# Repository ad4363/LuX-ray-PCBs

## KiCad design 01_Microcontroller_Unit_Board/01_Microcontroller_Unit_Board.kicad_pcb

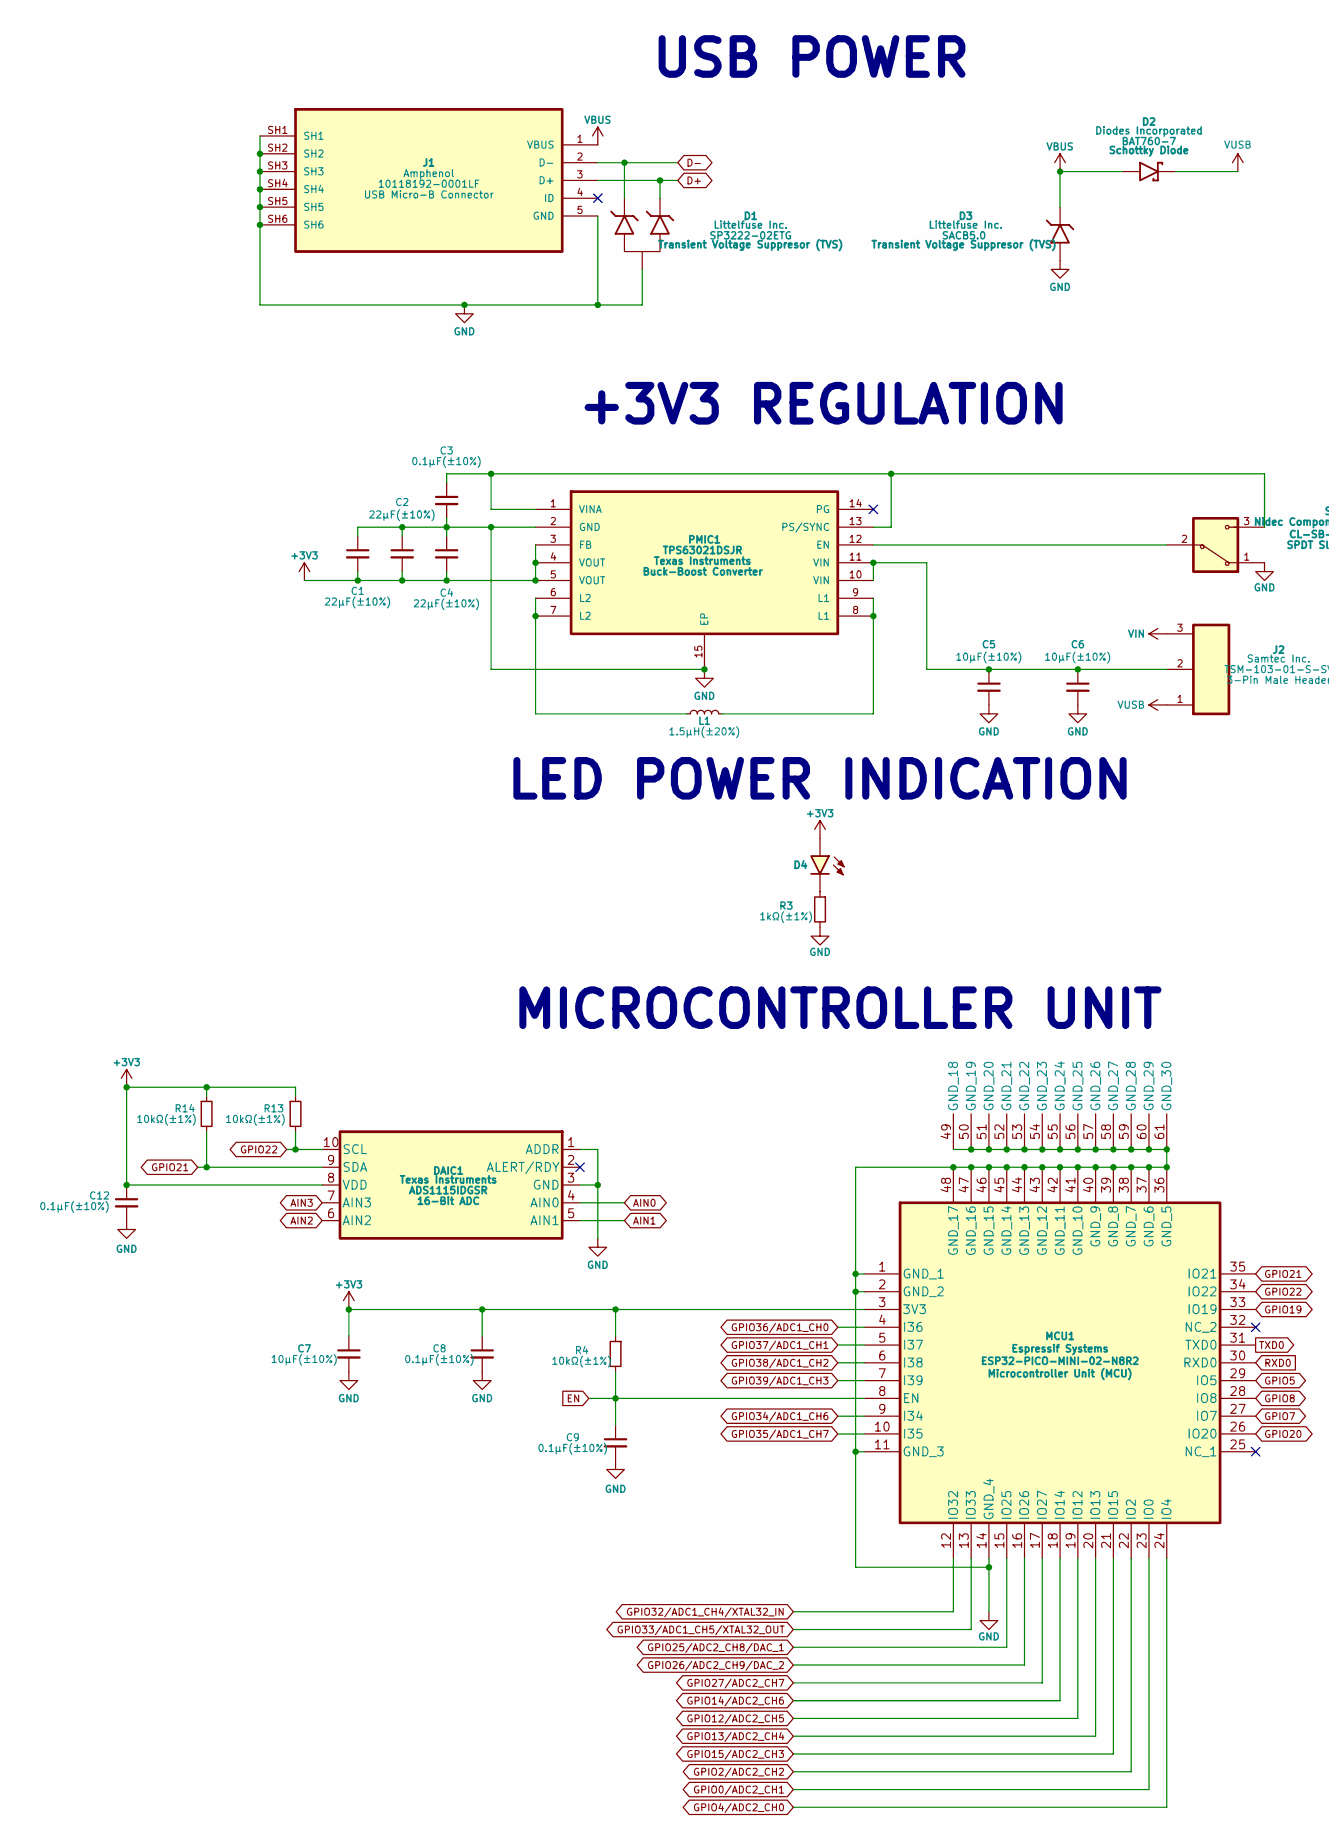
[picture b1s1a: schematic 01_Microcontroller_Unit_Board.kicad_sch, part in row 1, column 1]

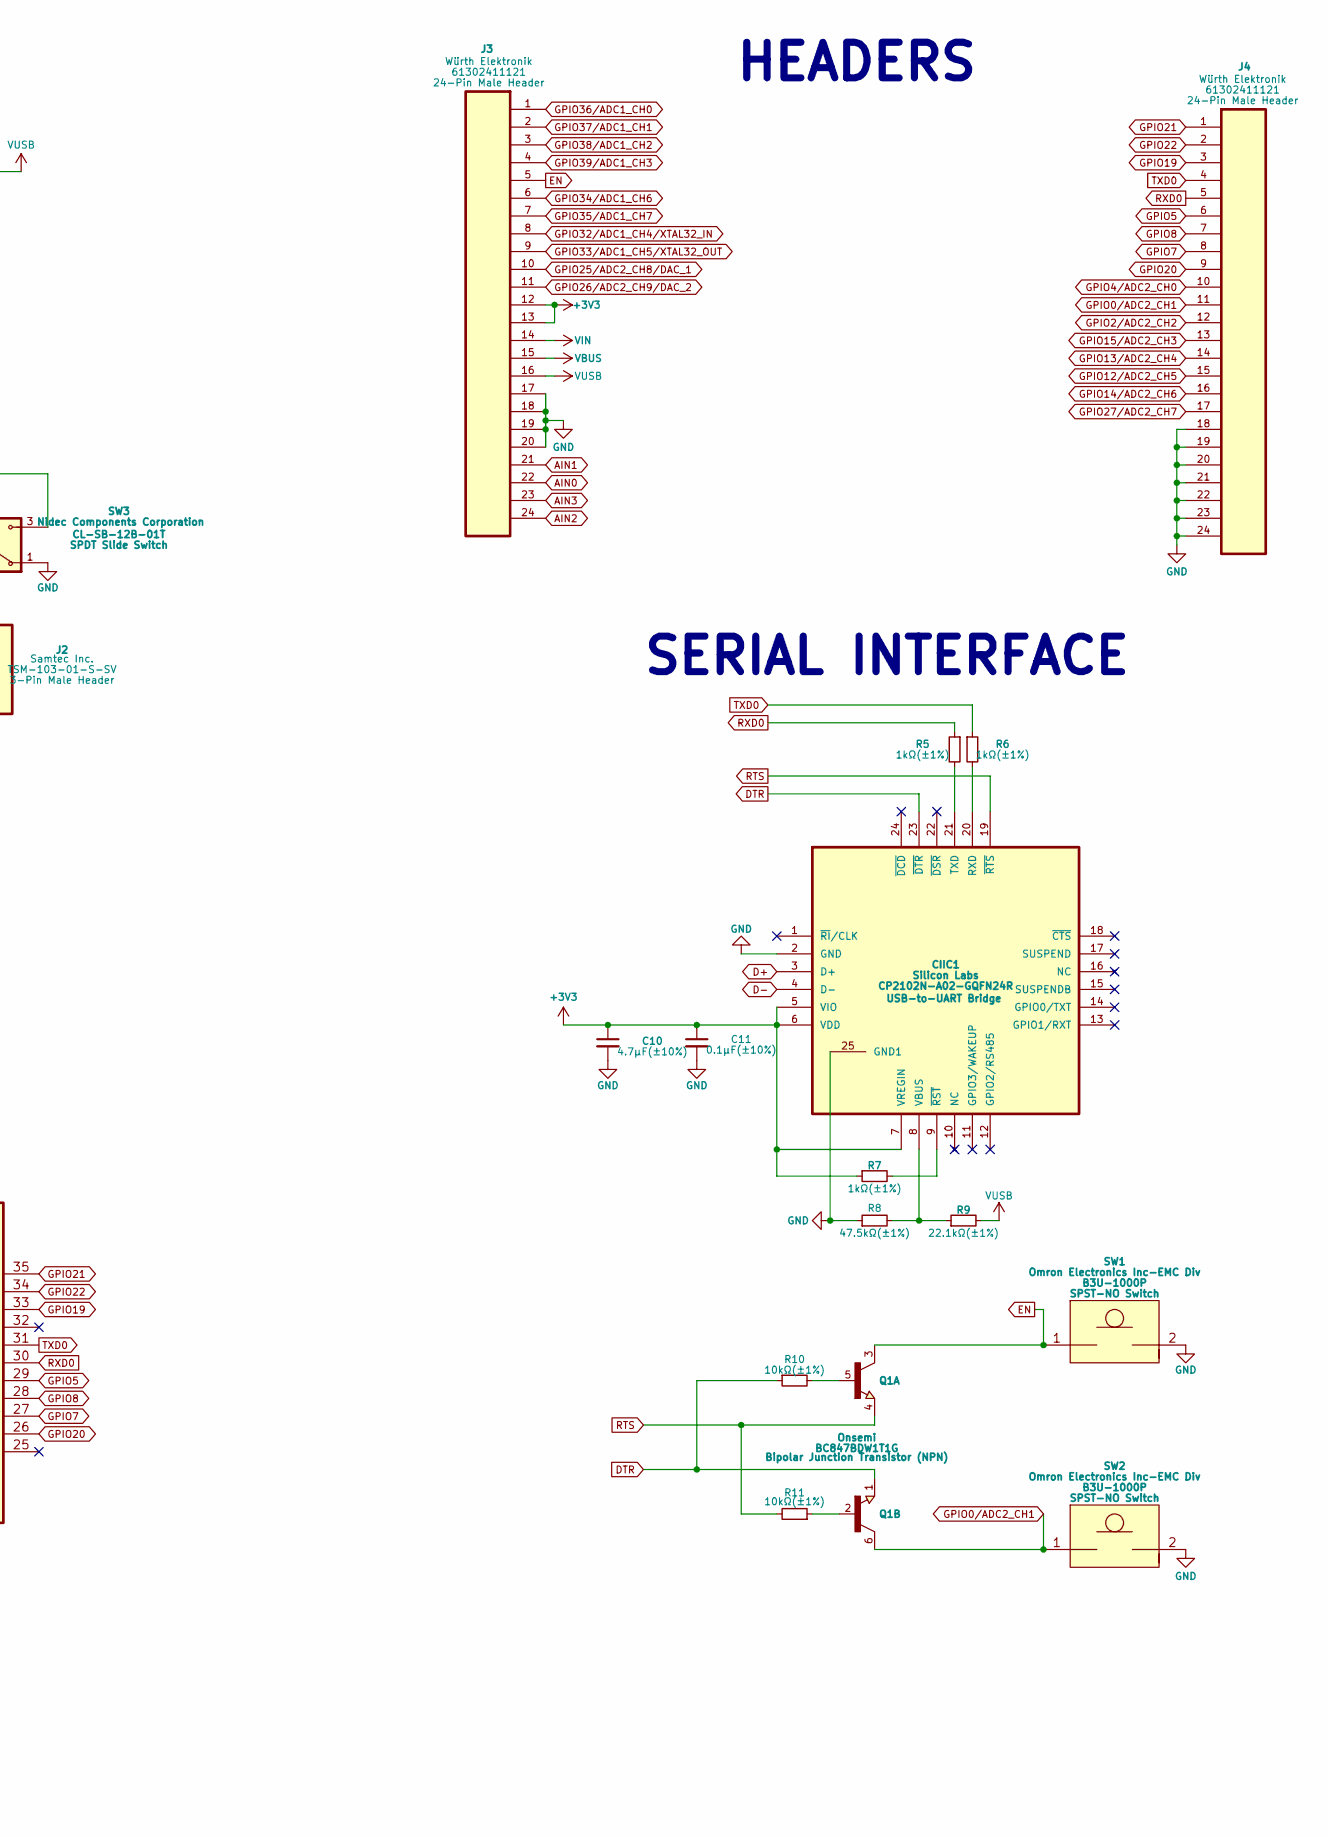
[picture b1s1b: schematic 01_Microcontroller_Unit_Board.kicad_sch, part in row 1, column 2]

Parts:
C1, C2, C4: 22µF(±10%); 1210 (3225 Metric); Manufacturer Part # GCM32EC71E226KE36K
C3, C8, C9, C11, C12: 0.1µF(±10%); 0402 (1005 Metric); Manufacturer Part # GCM155R71E104KE02D
C5, C6, C7: 10µF(±10%); 1210 (3225 Metric); Manufacturer Part # GCM32ER71E106KA57L
C10: 4.7µF(±10%); 1206 (3216 Metric); Manufacturer Part # GCM31CR71E475KA55K
CIIC1: CP2102N-A02-GQFN24R; 24-QFN; Manufacturer Part # CP2102N-A02-GQFN24R
D1: SP3222-02ETG; SOD-883; Manufacturer Part # SP3222-02ETG
D2: BAT760-7; SOD-323; Manufacturer Part # BAT760-7
D3: SACB5.0; SMB; Manufacturer Part # SACB5.0
D4: 150060GS75000; 0603 (1608 Metric); Manufacturer Part # 150060GS75000
DAIC1: ADS1115IDGSR; 10-VSSOP; Manufacturer Part # ADS1115IDGSR
J1: 10118192-0001LF; Amphenol_10118192-0001LF; Manufacturer Part # 10118192-0001LF
J2: TSM-103-01-S-SV; Samtec_TSM-103-01-S-SV; Manufacturer Part # TSM-103-01-S-SV
J3, J4: 61302411121; Wurth_61302411121; Manufacturer Part # 61302411121
L1: 1.5µH(±20%); Coilcraft_XFL4020-152MEC; Manufacturer Part # XFL4020-152MEC
MCU1: ESP32-PICO-MINI-02-N8R2; Espressif_ESP32-PICO-MINI-02-N8R2; Manufacturer Part # ESP32-PICO-MINI-02-N8R2
PMIC1: TPS63021; 14-VSON; Manufacturer Part # TPS63021DSJR
Q1: BC847BDW1T1G; SOT-363; Manufacturer Part # BC847BDW1T1G
R3, R5, R6, R7: 1kΩ(±1%); 0402 (1005 Metric); Manufacturer Part # CRCW04021K00FKED
R4, R10, R11, R13, R14: 10kΩ(±1%); 0402 (1005 Metric); Manufacturer Part # CRCW040210K0FKED
R8: 47.5kΩ(±1%); 0402 (1005 Metric); Manufacturer Part # CR0402-FX-4752GLF
R9: 22.1kΩ(±1%); 0402 (1005 Metric); Manufacturer Part # CRCW040222K1FKED
SW1, SW2: B3U-1000P; Omron_B3U-1000P; Manufacturer Part # B3U-1000P
SW3: CL-SB-12B-01T; Nidec_CL-SB-12B-01T; Manufacturer Part # CL-SB-12B-01T

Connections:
+3V3: C1.2, C2.2, C4.2, C7.1, C8.1, C10.1, C11.1, C12.1, CIIC1.5 (VIO), CIIC1.6 (VDD), CIIC1.7 (VREGIN), D4.A, DAIC1.8 (VDD), J3.12, J3.13, MCU1.3 (3V3), PMIC1.3 (FB), PMIC1.4 (VOUT), PMIC1.5 (VOUT), R4.1, R7.1, R13.1, R14.1; also elsewhere on the board
AIN0: DAIC1.4 (AIN0), J3.22
AIN1: DAIC1.5 (AIN1), J3.21
AIN2: DAIC1.6 (AIN2), J3.24
AIN3: DAIC1.7 (AIN3), J3.23
D+: CIIC1.3 (D+), D1.K2, J1.3 (D+)
D-: CIIC1.4 (D-), D1.K1, J1.2 (D-)
DTR: CIIC1.23 (~DTR), Q1.1, R10.1
EN: C9.1, J3.5, MCU1.8 (EN), Q1.3, R4.2, SW1.1
GND: C1.1, C2.1, C3.2, C4.1, C5.2, C6.2, C7.2, C8.2, C9.2, C10.2, C11.2, C12.2, CIIC1.2 (GND), CIIC1.25 (GND1), D1.A, D3.A, DAIC1.1 (ADDR), DAIC1.3 (GND), J1.5 (GND), J1.SH1, J1.SH2, J1.SH3, J1.SH4, J1.SH5, J1.SH6, J3.17, J3.18, J3.19, J3.20, J4.18, J4.19, J4.20, J4.21, J4.22, J4.23, J4.24, MCU1.1 (GND_1), MCU1.2 (GND_2), MCU1.11 (GND_3), MCU1.14 (GND_4), MCU1.36 (GND_5), MCU1.37 (GND_6), MCU1.38 (GND_7), MCU1.39 (GND_8), MCU1.40 (GND_9), MCU1.41 (GND_10), MCU1.42 (GND_11), MCU1.43 (GND_12), MCU1.44 (GND_13), MCU1.45 (GND_14), MCU1.46 (GND_15), MCU1.47 (GND_16), MCU1.48 (GND_17), MCU1.49 (GND_18), MCU1.50 (GND_19), MCU1.51 (GND_20), MCU1.52 (GND_21), MCU1.53 (GND_22), MCU1.54 (GND_23), MCU1.55 (GND_24), MCU1.56 (GND_25), MCU1.57 (GND_26), MCU1.58 (GND_27), MCU1.59 (GND_28), MCU1.60 (GND_29), MCU1.61 (GND_30), PMIC1.2 (GND), PMIC1.15 (EP), R3.2, R8.1, SW1.2, SW2.2, SW3.1
GPIO0/ADC2_CH1: J4.11, MCU1.23 (IO0), Q1.6, SW2.1
GPIO2/ADC2_CH2: J4.12, MCU1.22 (IO2)
GPIO4/ADC2_CH0: J4.10, MCU1.24 (IO4)
GPIO5: J4.6, MCU1.29 (IO5)
GPIO7: J4.8, MCU1.27 (IO7)
GPIO8: J4.7, MCU1.28 (IO8)
GPIO12/ADC2_CH5: J4.15, MCU1.19 (IO12)
GPIO13/ADC2_CH4: J4.14, MCU1.20 (IO13)
GPIO14/ADC2_CH6: J4.16, MCU1.18 (IO14)
GPIO15/ADC2_CH3: J4.13, MCU1.21 (IO15)
GPIO19: J4.3, MCU1.33 (IO19)
GPIO20: J4.9, MCU1.26 (IO20)
GPIO21: DAIC1.9 (SDA), J4.1, MCU1.35 (IO21), R14.2
GPIO22: DAIC1.10 (SCL), J4.2, MCU1.34 (IO22), R13.2
GPIO25/ADC2_CH8/DAC_1: J3.10, MCU1.15 (IO25)
GPIO26/ADC2_CH9/DAC_2: J3.11, MCU1.16 (IO26)
GPIO27/ADC2_CH7: J4.17, MCU1.17 (IO27)
GPIO32/ADC1_CH4/XTAL32_IN: J3.8, MCU1.12 (IO32)
GPIO33/ADC1_CH5/XTAL32_OUT: J3.9, MCU1.13 (IO33)
GPIO34/ADC1_CH6: J3.6, MCU1.9 (I34)
GPIO35/ADC1_CH7: DAIC1.2 (ALERT/RDY), J3.7, MCU1.10 (I35); also elsewhere on the board
GPIO36/ADC1_CH0: J3.1, MCU1.4 (I36)
GPIO37/ADC1_CH1: J3.2, MCU1.5 (I37)
GPIO38/ADC1_CH2: J3.3, MCU1.6 (I38)
GPIO39/ADC1_CH3: J3.4, MCU1.7 (I39)
unnamed: C5.1, C6.1, J2.2, PMIC1.10 (VIN), PMIC1.11 (VIN)
unnamed: CIIC1.20 (RXD), R6.2
unnamed: CIIC1.21 (TXD), R5.2
unnamed: CIIC1.8 (VBUS), R8.2, R9.1
unnamed: CIIC1.9 (~RST), R7.2
unnamed: D4.K, R3.1
unnamed: L1.1, PMIC1.6 (L2), PMIC1.7 (L2)
unnamed: L1.2, PMIC1.8 (L1), PMIC1.9 (L1)
unnamed: PMIC1.12 (EN), SW3.2
unnamed: C3.1, PMIC1.1 (VINA), PMIC1.13 (PS/SYNC), SW3.3
unnamed: Q1.2, R11.1
unnamed: Q1.5, R10.2
RTS: CIIC1.19 (~RTS), Q1.4, R11.2
RXD0: J4.5, MCU1.30 (RXD0), R5.1
TXD0: J4.4, MCU1.31 (TXD0), R6.1
VBUS: D2.A, D3.K, J1.1 (VBUS), J3.15
VIN: J2.3, J3.14
VUSB: D2.K, J2.1, J3.16, R9.2

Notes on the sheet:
HEADERS
USB POWER
MICROCONTROLLER UNIT
+3V3 REGULATION
SERIAL INTERFACE
LED POWER INDICATION

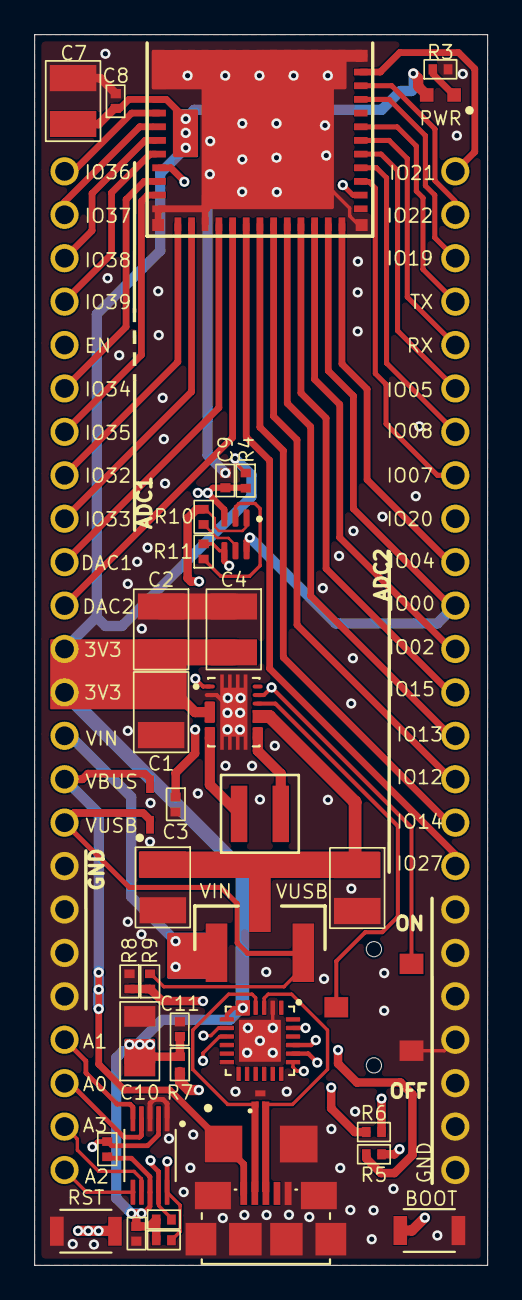
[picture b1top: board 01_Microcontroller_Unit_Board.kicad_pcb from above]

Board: 4 copper layers, 26.5 x 72.0 mm, 41 parts (0 on the bottom side), 53 nets.

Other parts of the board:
R12: 10kΩ(±1%); 0402 (1005 Metric)

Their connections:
+3V3: R12.1; also elsewhere on the board
GPIO35/ADC1_CH7: R12.2; also elsewhere on the board

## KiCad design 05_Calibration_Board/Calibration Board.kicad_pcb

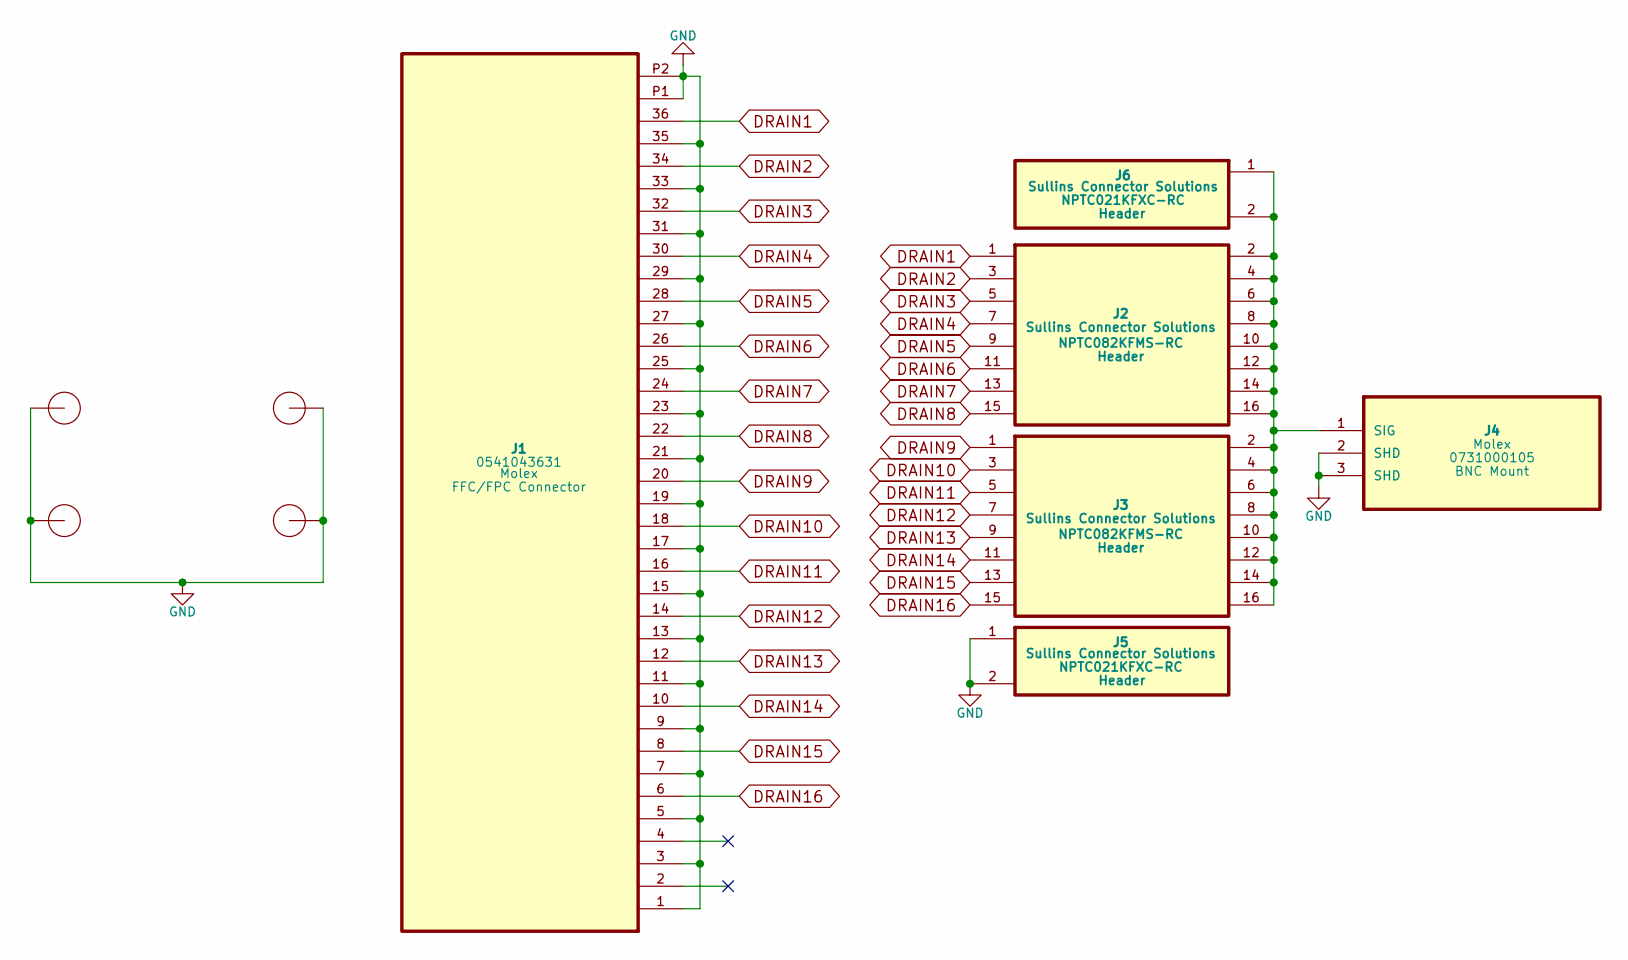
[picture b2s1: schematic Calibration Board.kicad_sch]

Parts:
J1: 0541043631; Manufacturer Part # 0541043631
J2, J3: NPTC082KFMS-RC; Manufacturer Part # NPTC082KFMS-RC
J4: 0731375003; 0731000105; Manufacturer Part # 0731000105
J5, J6: NPTC021KFXC-RC; Manufacturer Part # NPTC021KFXC-RC
MH1: Mounting Holes (Calibration)

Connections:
DRAIN1: J1.36, J2.1
DRAIN2: J1.34, J2.3
DRAIN3: J1.32, J2.5
DRAIN4: J1.30, J2.7
DRAIN5: J1.28, J2.9
DRAIN6: J1.26, J2.11
DRAIN7: J1.24, J2.13
DRAIN8: J1.22, J2.15
DRAIN9: J1.20, J3.1
DRAIN10: J1.18, J3.3
DRAIN11: J1.16, J3.5
DRAIN12: J1.14, J3.7
DRAIN13: J1.12, J3.9
DRAIN14: J1.10, J3.11
DRAIN15: J1.8, J3.13
DRAIN16: J1.6, J3.15
GND: J1.1, J1.3, J1.5, J1.7, J1.9, J1.11, J1.13, J1.15, J1.17, J1.19, J1.21, J1.23, J1.25, J1.27, J1.29, J1.31, J1.33, J1.35, J1.P1, J1.P2, J4.2 (SHD), J4.3 (SHD), J5.1, J5.2, MH1.MH1, MH1.MH2, MH1.MH3, MH1.MH4
unnamed: J2.2, J2.4, J2.6, J2.8, J2.10, J2.12, J2.14, J2.16, J3.2, J3.4, J3.6, J3.8, J3.10, J3.12, J3.14, J3.16, J4.1 (SIG), J6.1, J6.2

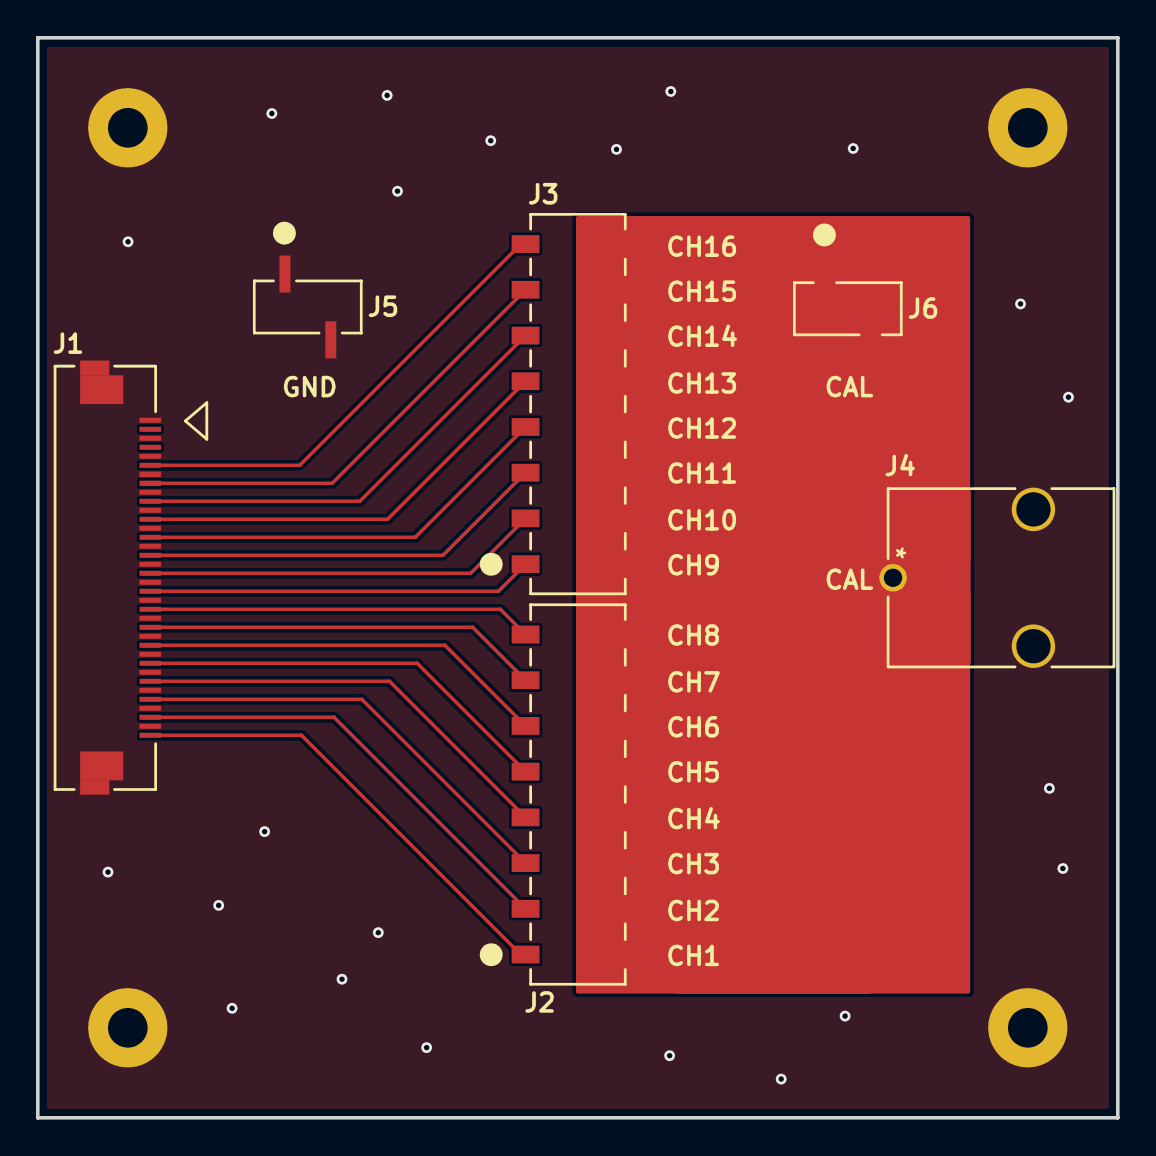
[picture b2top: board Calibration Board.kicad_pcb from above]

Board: 2 copper layers, 60.0 x 60.0 mm, 7 parts (0 on the bottom side), 18 nets.

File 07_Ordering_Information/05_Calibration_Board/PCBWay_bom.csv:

"#","Reference","Qty","Manufacturer","Manufacturer Part #","Supplier","Supplier Part #","Supplier Price ($)","Short Description","Category","Subcategory","Package","Type"
"1","J1","1","Molex","0541043631","DigiKey","WM8866CT-ND","3.03","CONN FFC FPC TOP 36POS 0.5MM R/A","Connector Assembly","FFC/FPC Connector","Nonstandard 38-pin","SMD"
"2","J2,J3","2","Sullins Connector Solutions","NPTC082KFMS-RC","DigiKey","S5678-ND","1.74","CONN HDR 16POS 0.1 TIN SMD","Connector Assembly","Header","Nonstandard 16-pin","SMD"
"3","J4","1","Molex","0731000105","DigiKey","WM5524-ND","2.05","CONN BNC RCPT R/A 50 OHM PCB","Connector Assembly","BNC Mount","Nonstandard 3-pin","Through Hole"
"4","J5,J6","2","Sullins Connector Solutions","NPTC021KFXC-RC","DigiKey","S5594-ND","0.51","CONN HDR 2POS 0.1 TIN SMD","Connector Assembly","Header","Nonstandard 2-pin","SMD"

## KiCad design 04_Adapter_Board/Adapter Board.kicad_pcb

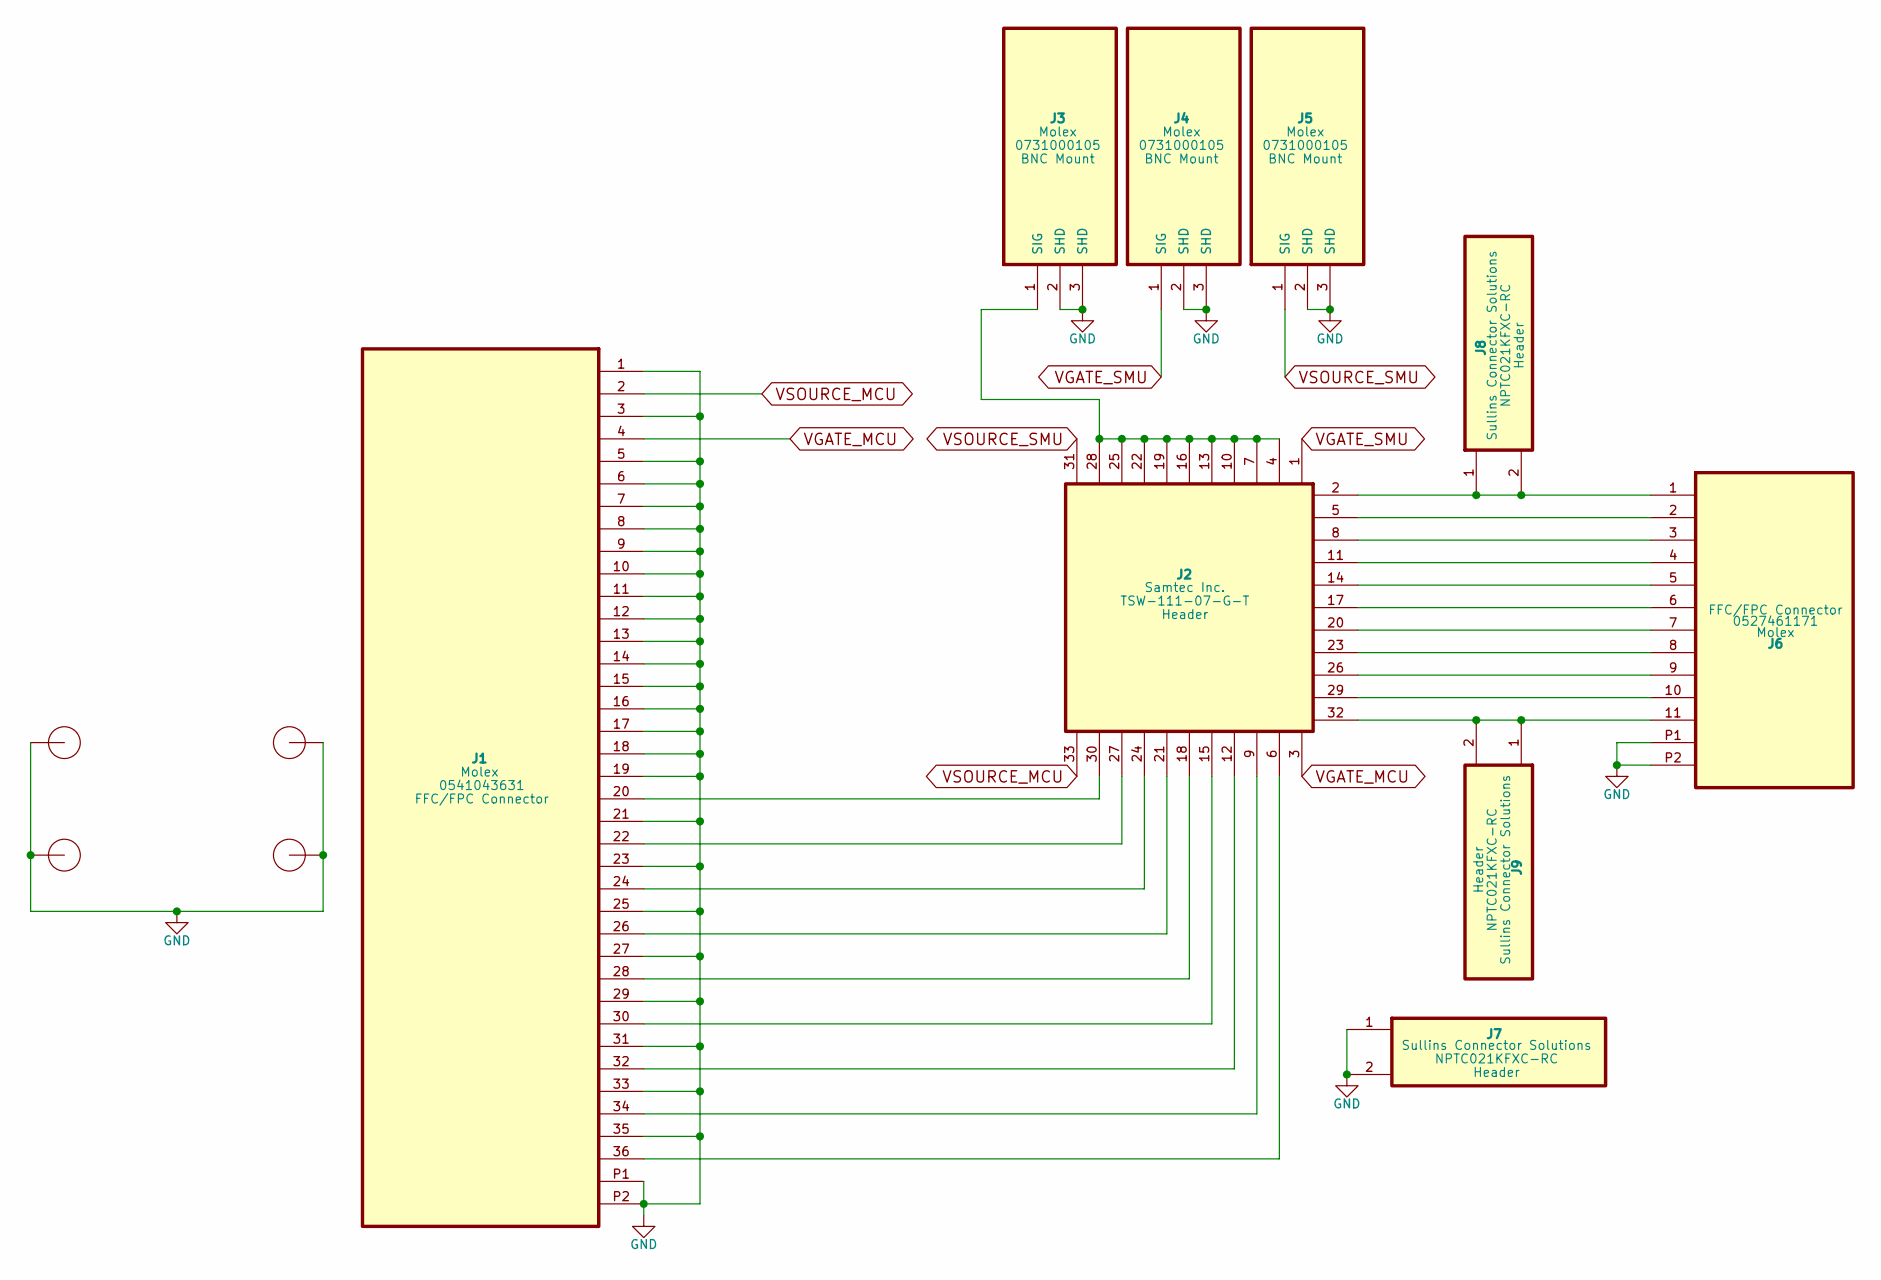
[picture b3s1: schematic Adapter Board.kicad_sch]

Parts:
J1: 0541043631; Manufacturer Part # 0541043631
J2: TSW-111-07-G-T; Manufacturer Part # TSW-111-07-G-T
J3, J4, J5: 0731375003; 0731000105; Manufacturer Part # 0731000105
J6: 0527461171; Manufacturer Part # 0527461171
J7, J8, J9: NPTC021KFXC-RC; Manufacturer Part # NPTC021KFXC-RC
MH1: Mounting Holes (Adapter)

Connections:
GND: J1.1, J1.3, J1.5, J1.6, J1.7, J1.8, J1.9, J1.10, J1.11, J1.12, J1.13, J1.14, J1.15, J1.16, J1.17, J1.18, J1.19, J1.21, J1.23, J1.25, J1.27, J1.29, J1.31, J1.33, J1.35, J1.P1, J1.P2, J3.2 (SHD), J3.3 (SHD), J4.2 (SHD), J4.3 (SHD), J5.2 (SHD), J5.3 (SHD), J6.P1, J6.P2, J7.1, J7.2, MH1.MH1, MH1.MH2, MH1.MH3, MH1.MH4
unnamed: J1.20, J2.30
unnamed: J1.22, J2.27
unnamed: J1.24, J2.24
unnamed: J1.26, J2.21
unnamed: J1.28, J2.18
unnamed: J1.30, J2.15
unnamed: J1.32, J2.12
unnamed: J1.34, J2.9
unnamed: J1.36, J2.6
unnamed: J2.2, J6.1, J8.1, J8.2
unnamed: J2.5, J6.2
unnamed: J2.8, J6.3
unnamed: J2.11, J6.4
unnamed: J2.14, J6.5
unnamed: J2.17, J6.6
unnamed: J2.20, J6.7
unnamed: J2.23, J6.8
unnamed: J2.26, J6.9
unnamed: J2.29, J6.10
unnamed: J2.32, J6.11, J9.1, J9.2
unnamed: J2.4, J2.7, J2.10, J2.13, J2.16, J2.19, J2.22, J2.25, J2.28, J3.1 (SIG)
VGATE_MCU: J1.4, J2.3
VGATE_SMU: J2.1, J4.1 (SIG)
VSOURCE_MCU: J1.2, J2.33
VSOURCE_SMU: J2.31, J5.1 (SIG)

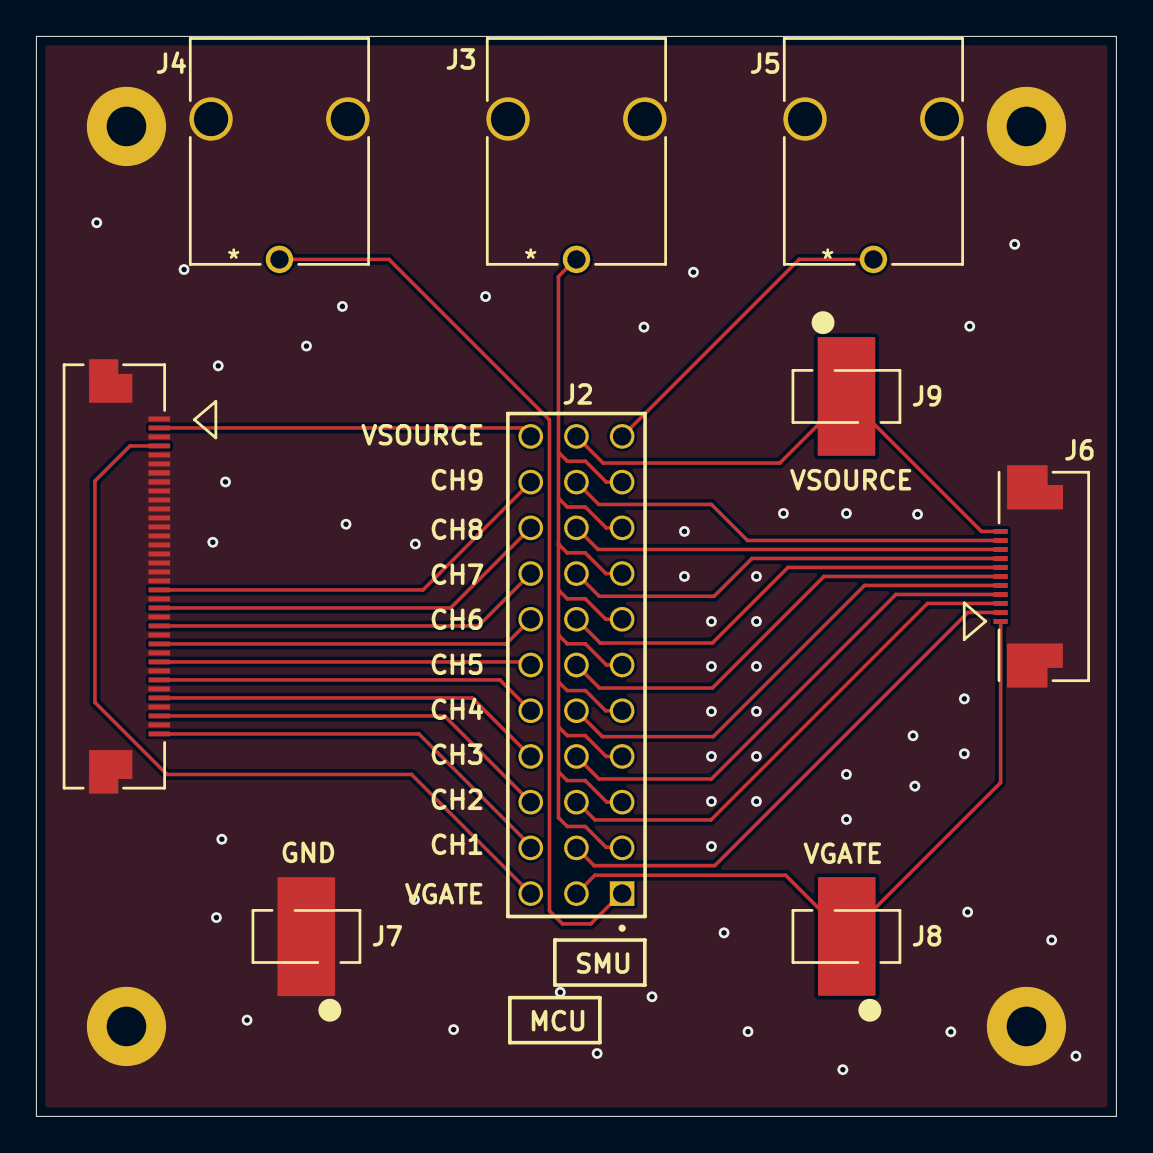
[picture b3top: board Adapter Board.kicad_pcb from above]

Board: 2 copper layers, 60.0 x 60.0 mm, 10 parts (0 on the bottom side), 26 nets.

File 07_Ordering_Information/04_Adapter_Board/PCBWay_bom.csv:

"#","Reference","Qty","Manufacturer","Manufacturer Part #","Supplier","Supplier Part #","Supplier Price ($)","Short Description","Category","Subcategory","Package","Type"
"1","J1","1","Molex","0541043631","DigiKey","WM8866CT-ND","3.03","CONN FFC FPC TOP 36POS 0.5MM R/A","Connector Assembly","FFC/FPC Connector","Nonstandard 38-pin","SMD"
"2","J2","1","Samtec Inc.","TSW-111-07-G-T","DigiKey","TSW-111-07-G-T-ND","2.68","CONN HEADER VERT 33POS 2.54MM","Connector Assembly","Header","Nonstandard 33-pin","Through Hole"
"3","J3,J4,J5","3","Molex","0731000105","DigiKey","WM5524-ND","2.05","CONN BNC RCPT R/A 50 OHM PCB","Connector Assembly","BNC Mount","Nonstandard 3-pin","Through Hole"
"4","J6","1","Molex","0527461171","DigiKey","WM8931CT-ND","1.50","CONN FFC BOTTOM 11POS 0.5MM R/A","Connector Assembly","FFC/FPC Connector","Nonstandard 13-pin","SMD"
"5","J7,J8,J9","3","Sullins Connector Solutions","NPTC021KFXC-RC","DigiKey","S5594-ND","0.51","CONN HDR 2POS 0.1 TIN SMD","Connector Assembly","Header","Nonstandard 2-pin","SMD"
